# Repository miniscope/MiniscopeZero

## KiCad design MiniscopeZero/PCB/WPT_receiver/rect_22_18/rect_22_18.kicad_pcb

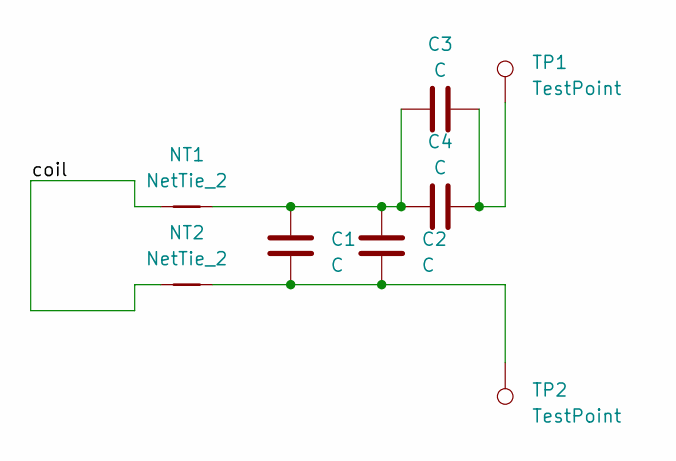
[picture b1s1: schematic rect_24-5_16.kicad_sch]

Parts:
C1, C2, C3, C4: C; C_0402_1005Metric
NT1, NT2: NetTie_2; NetTie-2_SMD_Pad0.5mm
TP1, TP2: TestPoint; TestPoint_THTPad_D1.0mm_Drill0.5mm

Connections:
/coil: NT1.1, NT2.2
unnamed: C1.1, C2.1, C3.1, C4.1, NT1.2
unnamed: C1.2, C2.2, NT2.1, TP2.1
unnamed: C3.2, C4.2, TP1.1

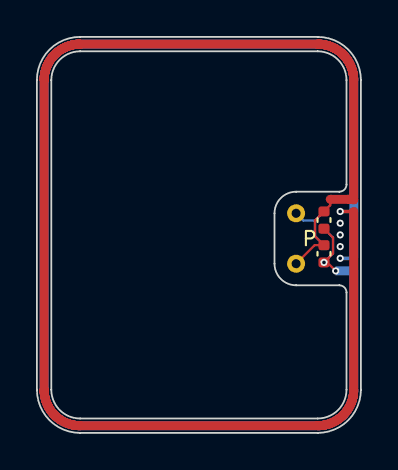
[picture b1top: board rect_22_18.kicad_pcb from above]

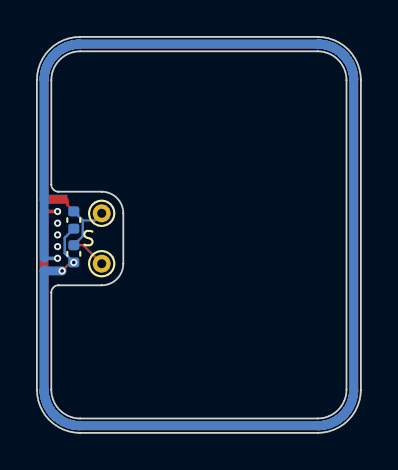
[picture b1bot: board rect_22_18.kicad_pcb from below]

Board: 6 copper layers, 18.0 x 22.0 mm, 8 parts (5 on the bottom side), 4 nets.
